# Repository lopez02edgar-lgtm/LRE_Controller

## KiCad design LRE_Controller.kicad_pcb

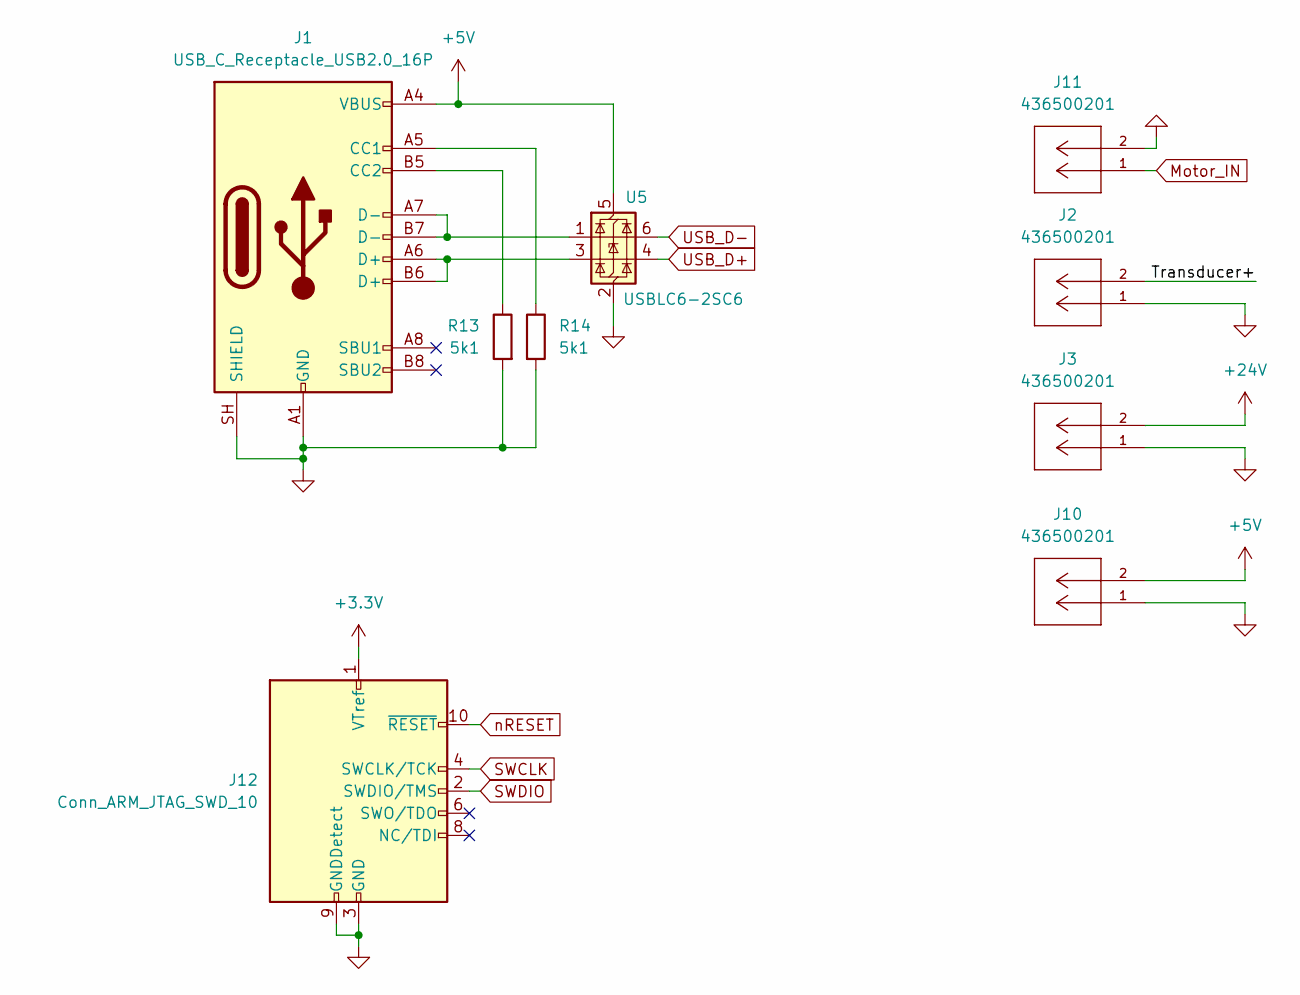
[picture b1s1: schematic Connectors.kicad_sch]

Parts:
J1: USB_C_Receptacle_USB2.0_16P; USB_C_Receptacle_GCT_USB4105-xx-A_16P_TopMnt_Horizontal
J2, J3, J10, J11: 436500201; CONN_SD-43650-001_02_MOL; MANUFACTURER_PART_NUMBER 436500201
J12: Conn_ARM_JTAG_SWD_10; PinHeader_2x05_P1.27mm_Vertical
R13, R14: 5k1; R_0402_1005Metric
U5: USBLC6-2SC6; SOT-23-6

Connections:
+3.3V: J12.1 (VTref); also elsewhere on the board
+5V: J1.A4 (VBUS), J1.A9 (VBUS), J1.B4 (VBUS), J1.B9 (VBUS), J10.2, U5.5 (VBUS); also elsewhere on the board
+24V: J3.2; also elsewhere on the board
/Connectors/Transducer+: J2.2
GND: J1.A1 (GND), J1.A12 (GND), J1.B1 (GND), J1.B12 (GND), J1.SH (SHIELD), J2.1, J3.1, J10.1, J11.2, J12.3 (GND), J12.5 (GND), J12.9 (GNDDetect), R13.2, R14.2, U5.2 (GND); also elsewhere on the board
Motor_IN: J11.1; also elsewhere on the board
unnamed: J1.A5 (CC1), R14.1
unnamed: J1.B5 (CC2), R13.1
unnamed: J1.A6 (D+), J1.B6 (D+), U5.3 (I/O2)
unnamed: J1.A7 (D-), J1.B7 (D-), U5.1 (I/O1)
SWCLK: J12.4 (SWCLK/TCK); also elsewhere on the board
SWDIO: J12.2 (SWDIO/TMS); also elsewhere on the board
USB_D+: U5.4 (I/O2); also elsewhere on the board
USB_D-: U5.6 (I/O1); also elsewhere on the board
nRESET: J12.10 (~RESET); also elsewhere on the board

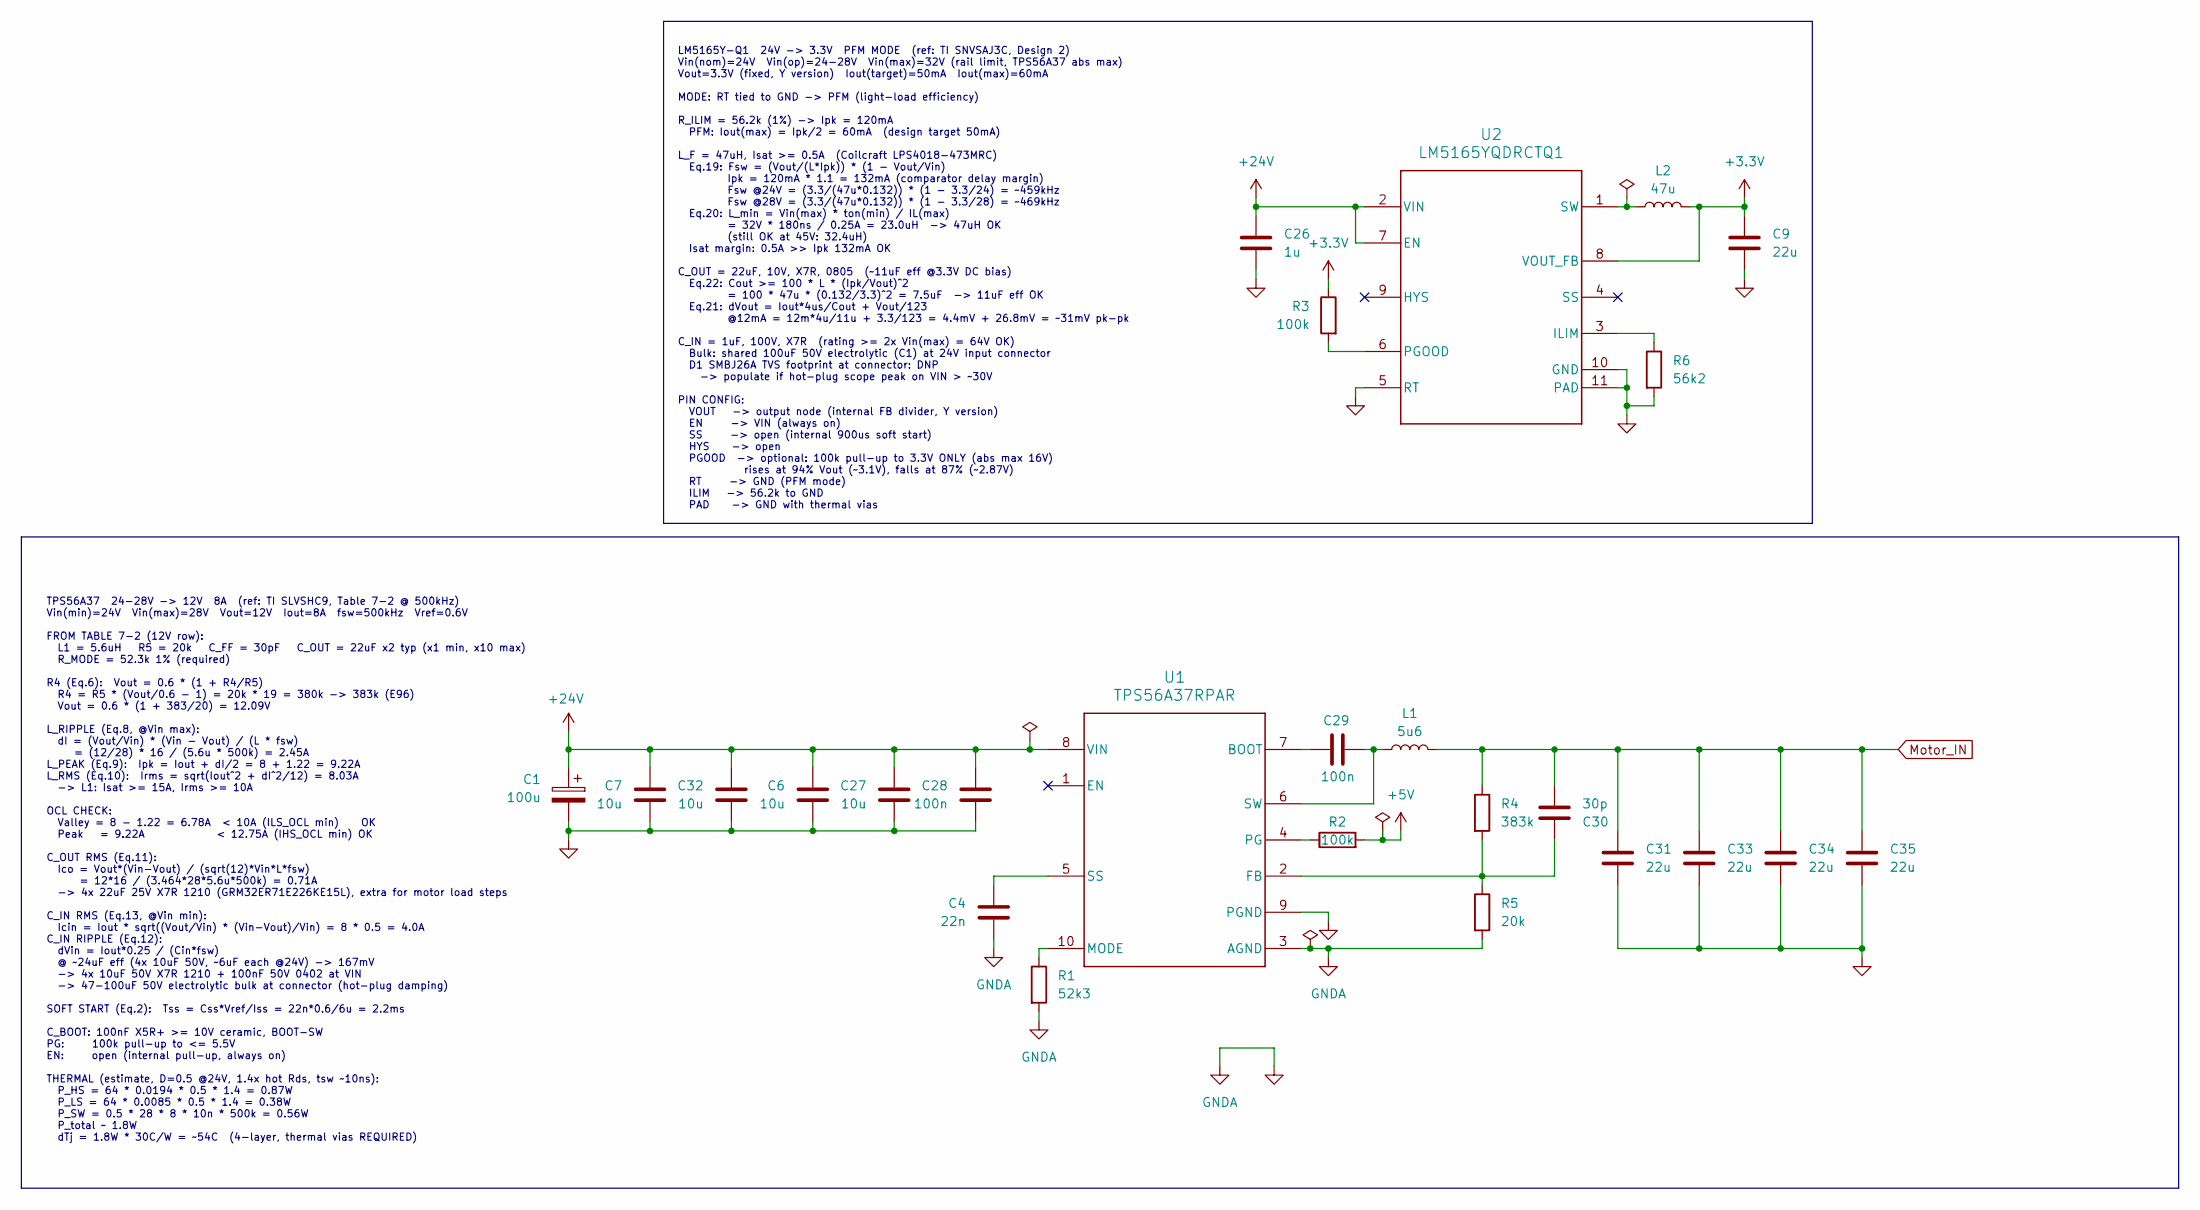
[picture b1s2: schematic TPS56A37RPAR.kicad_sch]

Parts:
C1: 100u; CAP_EEFK_J16_PAN
C4: 22n; C_0402_1005Metric
C6, C7, C27, C32: 10u; C_1210_3225Metric
C9: 22u; C_0402_1005Metric
C26: 1u; C_0805_2012Metric
C28: 100n; C_1210_3225Metric
C29: 100n; C_0805_2012Metric
C30: 30p; C_0402_1005Metric
C31, C33, C34, C35: 22u; C_1210_3225Metric
L1: 5u6; L_Wurth_WE-HCI-1890
L2: 47u; IND_LPS4018-473MRC
R1: 52k3; R_0402_1005Metric
R2, R3: 100k; R_0402_1005Metric
R4: 383k; R_0402_1005Metric
R5: 20k; R_0402_1005Metric
R6: 56k2; R_0402_1005Metric
U1: TPS56A37RPAR; RPA0010A-MFG
U2: LM5165YQDRCTQ1; DRC0010J

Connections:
+3.3V: C9.2, L2.2, R3.1, U2.8 (VOUT_FB); also elsewhere on the board
+5V: R2.2; also elsewhere on the board
+24V: C1.1, C6.2, C7.2, C26.2, C27.2, C28.2, C32.2, U1.8 (VIN), U2.2 (VIN), U2.7 (EN); also elsewhere on the board
GND: C1.2, C4.1, C6.1, C7.1, C9.1, C26.1, C27.1, C28.1, C31.1, C32.1, C33.1, C34.1, C35.1, R1.2, R5.2, R6.2, U1.3 (AGND), U1.9 (PGND), U2.5 (RT), U2.10 (GND), U2.11 (PAD); also elsewhere on the board
Motor_IN: C30.1, C31.2, C33.2, C34.2, C35.2, L1.2, R4.1; also elsewhere on the board
unnamed: C29.2, U1.7 (BOOT)
unnamed: C30.2, R4.2, R5.1, U1.2 (FB)
unnamed: R1.1, U1.10 (MODE)
unnamed: R2.1, U1.4 (PG)
unnamed: C4.2, U1.5 (SS)
unnamed: C29.1, L1.1, U1.6 (SW)
unnamed: R6.1, U2.3 (ILIM)
unnamed: R3.2, U2.6 (PGOOD)
unnamed: L2.1, U2.1 (SW)

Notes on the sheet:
LM5165Y-Q1 24V -> 3.3V PFM MODE (ref: TI SNVSAJ3C, Design 2) Vin(nom)=24V Vin(op)=24-28V Vin(max)=32V (rail limit, TPS56A37 abs max) Vout=3.3V (fixed, Y version) Iout(target)=50mA Iout(max)=60mA MODE: RT tied to GND -> PFM (light-load efficiency) R_ILIM = 56.2k (1%) -> Ipk = 120mA PFM: Iout(max) = 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
TPS56A37 24-28V -> 12V 8A (ref: TI SLVSHC9, Table 7-2 @ 500kHz) Vin(min)=24V Vin(max)=28V Vout=12V Iout=8A fsw=500kHz Vref=0.6V FROM TABLE 7-2 (12V row): L1 = 5.6uH R5 = 20k C_FF = 30pF C_OUT = 22uF x2 typ (x1 min, x10 max) R_MODE = 52.3k 1% (required) R4 (Eq.6): Vout = 0.6 * (1 + R4/R5) R4 = R5 * 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

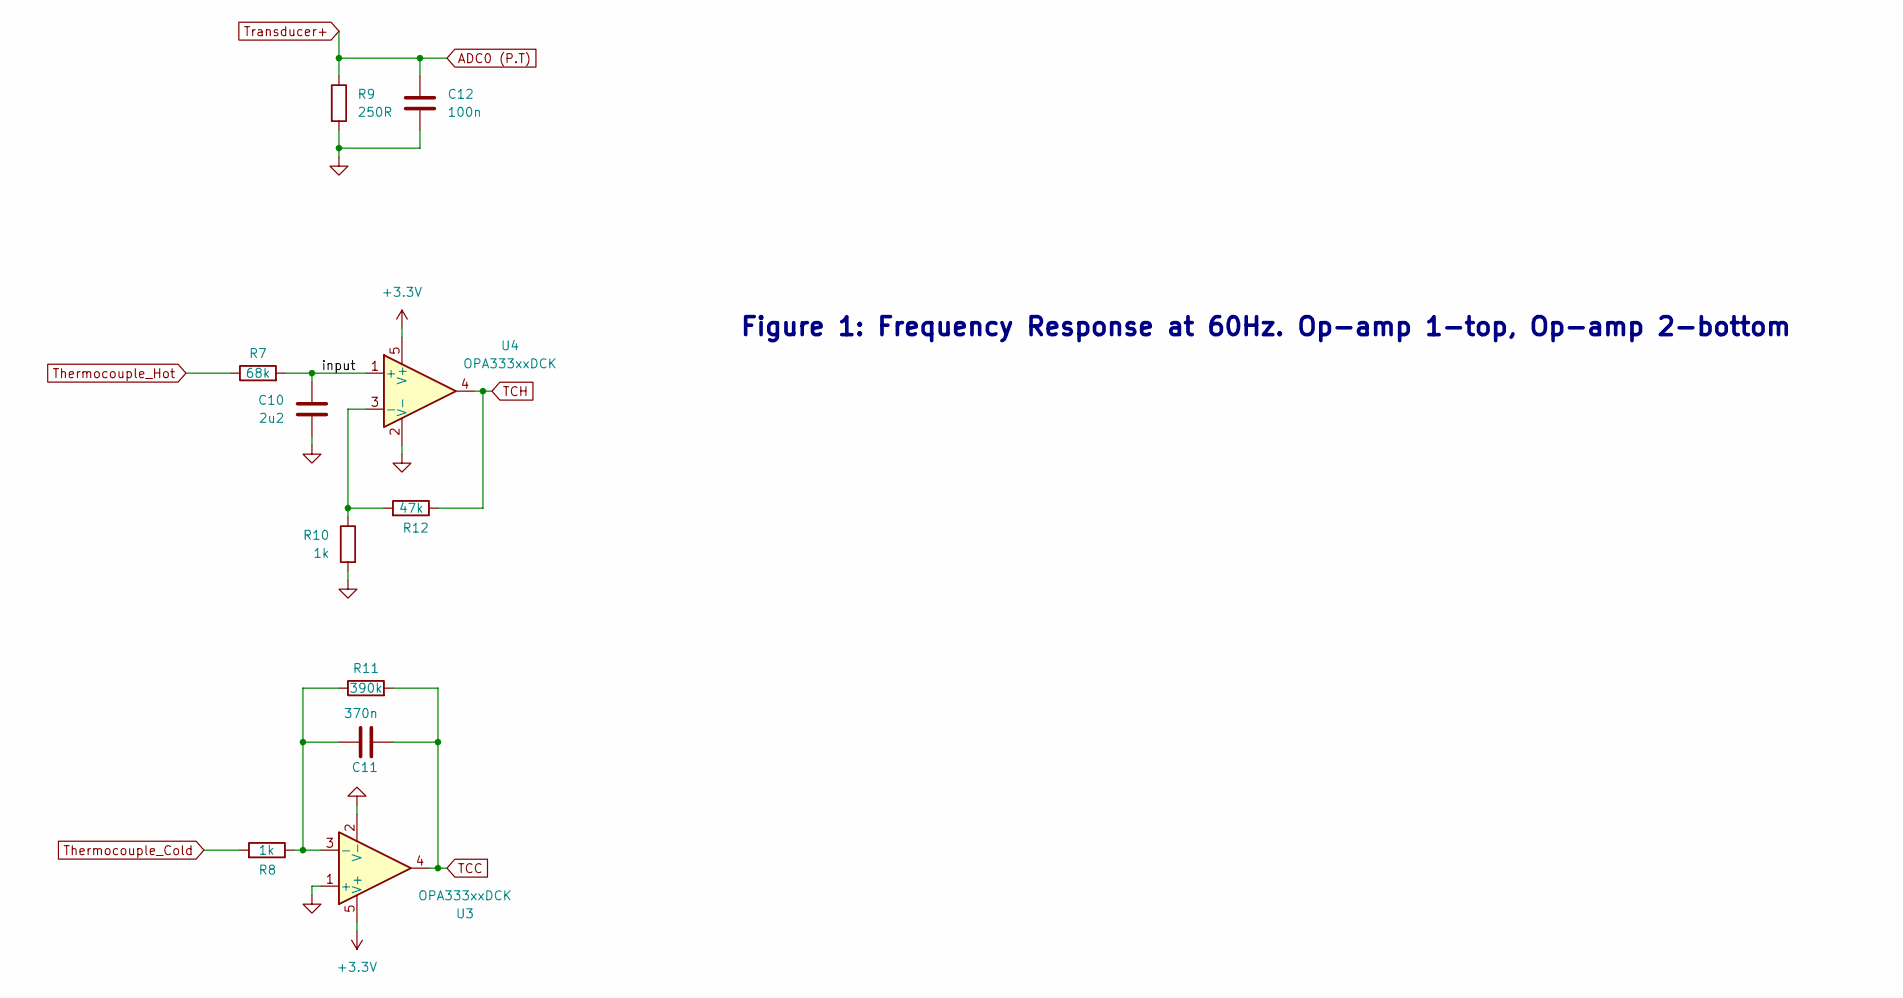
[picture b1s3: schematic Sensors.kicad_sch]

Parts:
C10: 2u2; C_0402_1005Metric
C11: 370n; C_0402_1005Metric
C12: 100n; C_0402_1005Metric
R7: 68k; R_0402_1005Metric
R8, R10: 1k; R_0402_1005Metric
R9: 250R; R_0402_1005Metric
R11: 390k; R_0402_1005Metric
R12: 47k; R_0402_1005Metric
U3, U4: OPA333xxDCK; SOT-353_SC-70-5

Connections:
+3.3V: U3.5 (V+), U4.5 (V+); also elsewhere on the board
/Sensors/input: C10.1, R7.2, U4.1 (+)
ADC0 (P.T): C12.1, R9.1; also elsewhere on the board
GND: C10.2, C12.2, R9.2, R10.2, U3.1 (+), U3.2 (V-), U4.2 (V-); also elsewhere on the board
unnamed: C11.1, R8.1, R11.1, U3.3 (-)
unnamed: R10.1, R12.2, U4.3 (-)
TCC: C11.2, R11.2, U3.4; also elsewhere on the board
TCH: R12.1, U4.4; also elsewhere on the board
Thermocouple_Cold: R8.2
Thermocouple_Hot: R7.1

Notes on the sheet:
Figure 1: Frequency Response at 60Hz. Op-amp 1-top, Op-amp 2-bottom

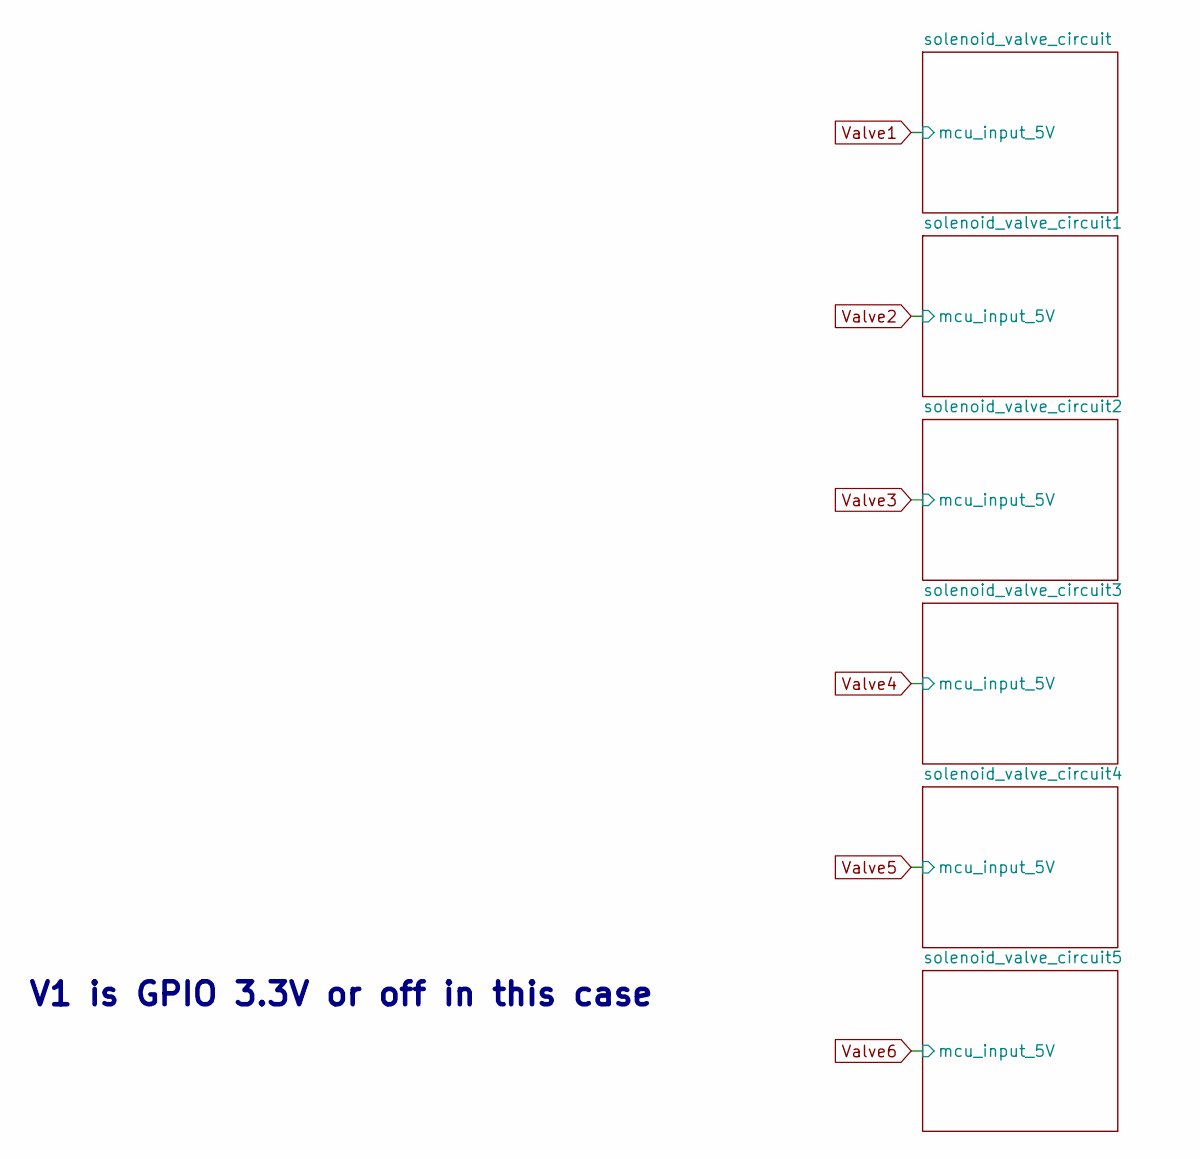
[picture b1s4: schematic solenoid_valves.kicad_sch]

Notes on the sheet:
V1 is GPIO 3.3V or off in this case

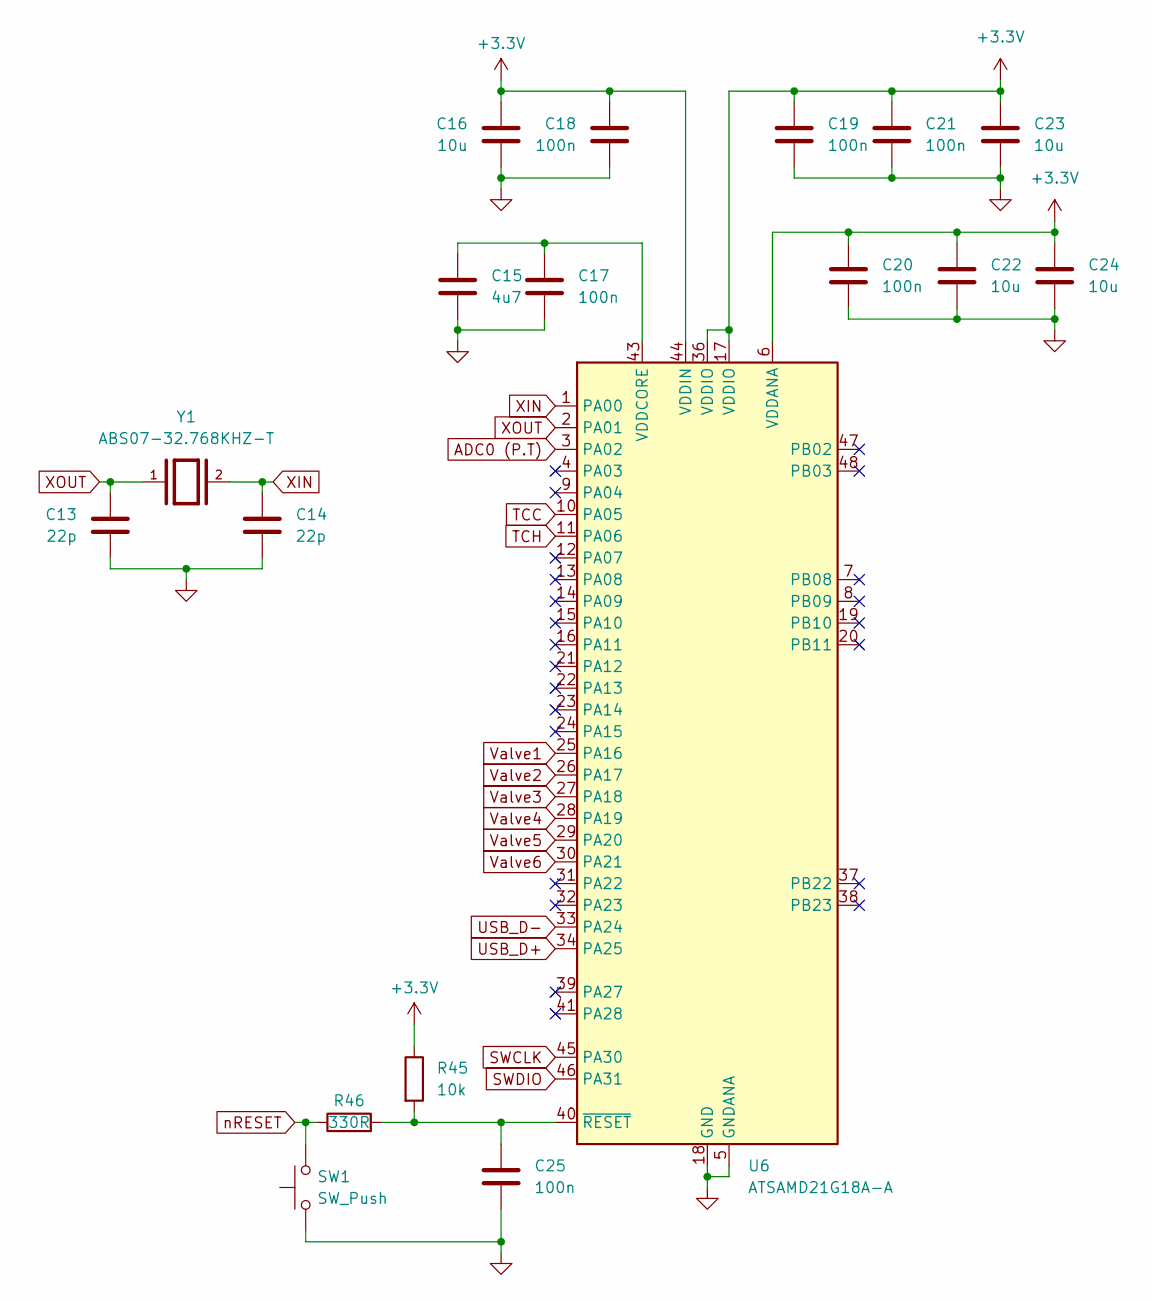
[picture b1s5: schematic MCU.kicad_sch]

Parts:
C13, C14: 22p; C_0402_1005Metric
C15: 4u7; C_0402_1005Metric
C16, C22, C23, C24: 10u; C_0402_1005Metric
C17, C18, C19, C20, C21, C25: 100n; C_0402_1005Metric
R45: 10k; R_0402_1005Metric
R46: 330R; R_0402_1005Metric
SW1: SW_Push; SW_SPST_B3S-1000
U6: ATSAMD21G18A-A; TQFP-48_7x7mm_P0.5mm
Y1: ABS07-32.768KHZ-T; XTAL_ABS07-32.768KHZ-T; PARTREV 08.19.15

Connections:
+3.3V: C16.1, C18.1, C19.1, C20.1, C21.1, C22.1, C23.1, C24.1, R45.1, U6.6 (VDDANA), U6.17 (VDDIO), U6.36 (VDDIO), U6.44 (VDDIN); also elsewhere on the board
ADC0 (P.T): U6.3 (PA02); also elsewhere on the board
GND: C13.2, C14.2, C15.2, C16.2, C17.2, C18.2, C19.2, C20.2, C21.2, C22.2, C23.2, C24.2, C25.2, SW1.1, U6.5 (GNDANA), U6.18 (GND), U6.35 (GND), U6.42 (GND); also elsewhere on the board
unnamed: C15.1, C17.1, U6.43 (VDDCORE)
unnamed: C25.1, R45.2, R46.2, U6.40 (~RESET)
SWCLK: U6.45 (PA30); also elsewhere on the board
SWDIO: U6.46 (PA31); also elsewhere on the board
TCC: U6.10 (PA05); also elsewhere on the board
TCH: U6.11 (PA06); also elsewhere on the board
USB_D+: U6.34 (PA25); also elsewhere on the board
USB_D-: U6.33 (PA24); also elsewhere on the board
Valve1: U6.25 (PA16); also elsewhere on the board
Valve2: U6.26 (PA17); also elsewhere on the board
Valve3: U6.27 (PA18); also elsewhere on the board
Valve4: U6.28 (PA19); also elsewhere on the board
Valve5: U6.29 (PA20); also elsewhere on the board
Valve6: U6.30 (PA21); also elsewhere on the board
XIN: C14.1, U6.1 (PA00), Y1.2
XOUT: C13.1, U6.2 (PA01), Y1.1
nRESET: R46.1, SW1.2; also elsewhere on the board

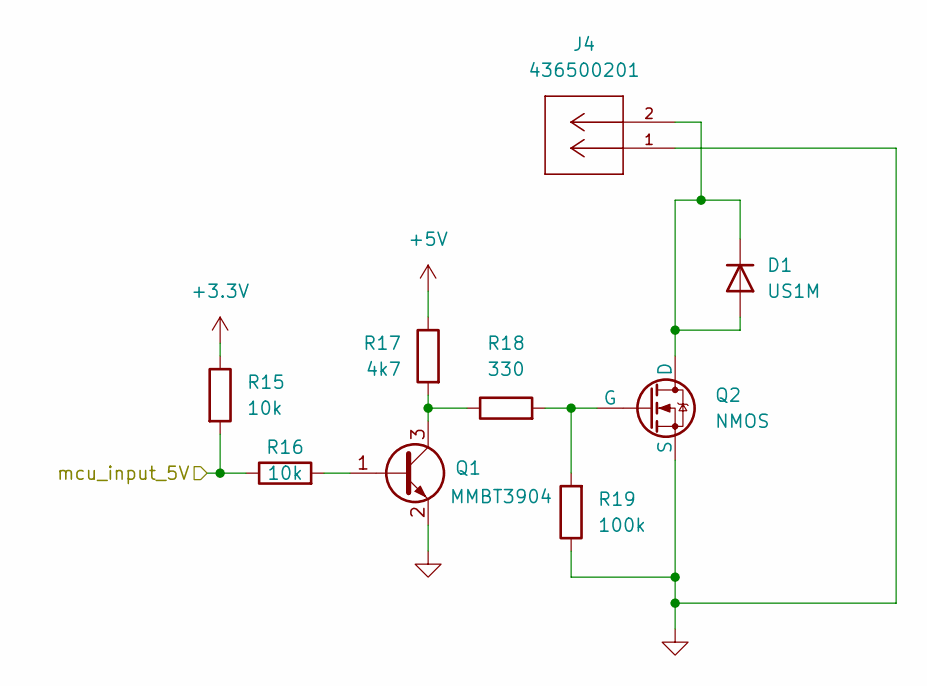
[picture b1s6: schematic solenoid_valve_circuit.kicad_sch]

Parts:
D1: US1M; D_SMA
J4: 436500201; CONN_SD-43650-001_02_MOL; MANUFACTURER_PART_NUMBER 436500201
Q1: MMBT3904; SOT-23
Q2: NMOS; SOT230P700X185-4N
R15, R16: 10k; R_0402_1005Metric
R17: 4k7; R_0402_1005Metric
R18: 330; R_0402_1005Metric
R19: 100k; R_0402_1005Metric

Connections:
+3.3V: R15.1; also elsewhere on the board
+5V: R17.1; also elsewhere on the board
GND: J4.1, Q1.2 (E), Q2.3 (S), R19.1; also elsewhere on the board
unnamed: D1.1 (K), D1.2 (A), J4.2, Q2.1 (D)
unnamed: Q1.1 (B), R16.2
unnamed: Q1.3 (C), R17.2, R18.1
unnamed: Q2.2 (G), R18.2, R19.2
Valve1: R15.2, R16.1; also elsewhere on the board

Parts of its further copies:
D2, D3, D4, D5, D6: US1M; D_SMA
J5, J6, J7, J8, J9: 436500201; CONN_SD-43650-001_02_MOL; MANUFACTURER_PART_NUMBER 436500201
Q3, Q5, Q7, Q9, Q11: MMBT3904; SOT-23
Q4, Q6, Q8, Q10, Q12: NMOS; SOT230P700X185-4N
R20, R21, R25, R26, R30, R31, R35, R36, R40, R41: 10k; R_0402_1005Metric
R22, R27, R32, R37, R42: 4k7; R_0402_1005Metric
R23, R28, R33, R38, R43: 330; R_0402_1005Metric
R24, R29, R34, R39, R44: 100k; R_0402_1005Metric

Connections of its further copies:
+3.3V: R20.1, R25.1, R30.1, R35.1, R40.1; also elsewhere on the board
+5V: R22.1, R27.1, R32.1, R37.1, R42.1; also elsewhere on the board
GND: J5.1, J6.1, J7.1, J8.1, J9.1, Q3.2 (E), Q4.3 (S), Q5.2 (E), Q6.3 (S), Q7.2 (E), Q8.3 (S), Q9.2 (E), Q10.3 (S), Q11.2 (E), Q12.3 (S), R24.1, R29.1, R34.1, R39.1, R44.1; also elsewhere on the board
unnamed: D2.1 (K), D2.2 (A), J5.2, Q4.1 (D)
unnamed: D3.1 (K), D3.2 (A), J6.2, Q6.1 (D)
unnamed: D4.1 (K), D4.2 (A), J7.2, Q8.1 (D)
unnamed: D5.1 (K), D5.2 (A), J8.2, Q10.1 (D)
unnamed: D6.1 (K), D6.2 (A), J9.2, Q12.1 (D)
unnamed: Q3.1 (B), R21.2
unnamed: Q3.3 (C), R22.2, R23.1
unnamed: Q4.2 (G), R23.2, R24.2
unnamed: Q5.1 (B), R26.2
unnamed: Q5.3 (C), R27.2, R28.1
unnamed: Q6.2 (G), R28.2, R29.2
unnamed: Q7.1 (B), R31.2
unnamed: Q7.3 (C), R32.2, R33.1
unnamed: Q8.2 (G), R33.2, R34.2
unnamed: Q9.1 (B), R36.2
unnamed: Q9.3 (C), R37.2, R38.1
unnamed: Q10.2 (G), R38.2, R39.2
unnamed: Q11.1 (B), R41.2
unnamed: Q11.3 (C), R42.2, R43.1
unnamed: Q12.2 (G), R43.2, R44.2
Valve2: R20.2, R21.1; also elsewhere on the board
Valve3: R25.2, R26.1; also elsewhere on the board
Valve4: R30.2, R31.1; also elsewhere on the board
Valve5: R35.2, R36.1; also elsewhere on the board
Valve6: R40.2, R41.1; also elsewhere on the board

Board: 4 copper layers, 117 parts (0 on the bottom side), 63 nets, no tracks yet.
